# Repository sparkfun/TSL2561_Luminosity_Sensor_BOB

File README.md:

**NOTE:** *This product has been retired from our catalog. If you are looking for more up-to-date info, please check out some of these resources to see how other users are still hacking and improving on this product.*
* *[SparkFun Forum](https://forum.sparkfun.com/)*
* *[Comments Here on GitHub](https://github.com/sparkfun/SparkFun_TSL2561_Arduino_Library/issues)*
* *[IRC Channel](https://www.sparkfun.com/news/263)*

SparkFun TSL2561 Luminosity Sensor Breakout Board
============================================

[*TSL2561 Luminosity Sensor Breakout (SEN-12055)*](https://www.sparkfun.com/products/12055)

This is a breakout board for the AMS/TAOS TSL2561 Luminosity sensor.
This illumination sensor has a flat response across most of the visible spectrum and has an adjustable integration time. 
It communicates via I2C and runs at 3.3V. 

Repository Contents
-------------------
* **/Documentation** - Datasheets and additional information 
* **/Hardware** - Eagle design files (.brd, .sch)
* **/Libraries** - Libraries for use with the TSL2561
* **/Production** - Production panel files (.brd)

Documentation
--------------
* **[Library](https://github.com/sparkfun/SparkFun_TSL2561_Arduino_Library)** - Arduino library for the TSL2561.
* **[Hookup Guide](https://learn.sparkfun.com/tutorials/tsl2561-luminosity-sensor-hookup-guide)** - Basic hookup guide for the TSL2561 Breakout.
* **[SparkFun Fritzing repo](https://github.com/sparkfun/Fritzing_Parts)** - Fritzing diagrams for SparkFun products.
* **[SparkFun 3D Model repo](https://github.com/sparkfun/3D_Models)** - 3D models of SparkFun products. 

License Information
-------------------
This product is _**open source**_! 

The **hardware** is released under [Creative Commons ShareAlike 4.0 International](https://creativecommons.org/licenses/by-sa/4.0/).

The **code** is beerware; if you see me (or any other SparkFun employee) at the local, and you've found our code helpful, please buy us a round!

Please use, reuse, and modify these files as you see fit. Please maintain attribution to SparkFun Electronics and release anything derivative under the same license.

Distributed as-is; no warranty is given.

- Your friends at SparkFun.

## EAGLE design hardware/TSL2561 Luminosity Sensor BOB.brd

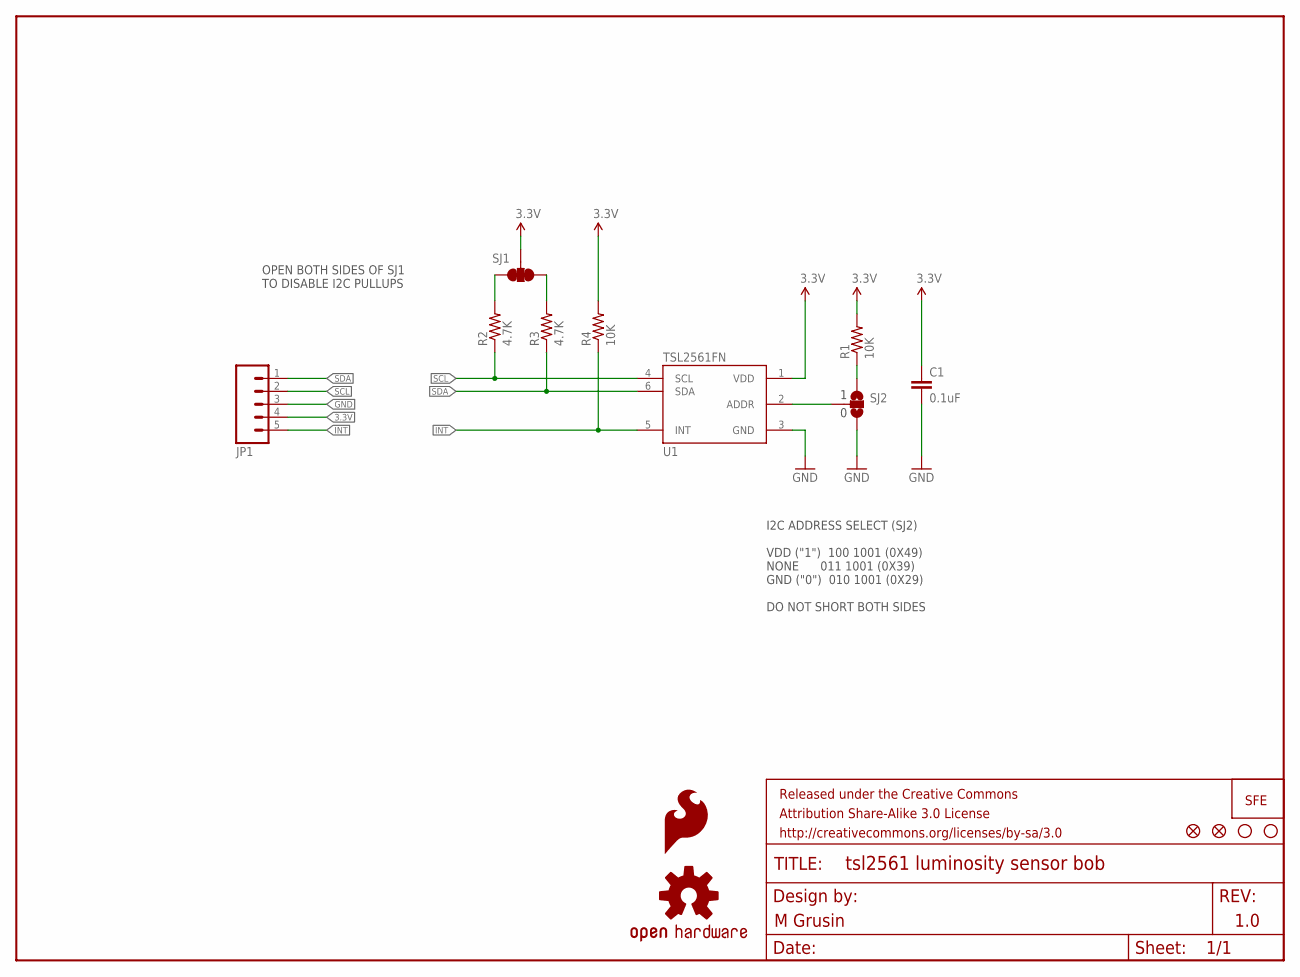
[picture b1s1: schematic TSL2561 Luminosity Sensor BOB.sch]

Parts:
C1: 0.1uF; 0603-CAP
FID1, FID2: FIDUCIALUFIDUCIAL; MICRO-FIDUCIAL
FRAME1: FRAME-LETTER; CREATIVE_COMMONS
JP1: M05_ROUNDONLY_NOSILK; 1X05_ROUNDONLY_NOSILK
LOGO1: OSHW-LOGOS; OSHW-LOGO-S
LOGO2: LOGO-SFENW2; SFE-NEW-WEB
LOGO3: SFE_LOGO_FLAME.1_INCH; SFE_LOGO_FLAME_.1
R1, R4: 10K; 0603-RES
R2, R3: 4.7K; 0603-RES
SJ1: SOLDERJUMPER_2WAYPASTE1&2&3; SJ_3_PASTE1&2&3
SJ2: SOLDERJUMPER_2WAYS; SJ_3
STANDOFF1, STANDOFF2: STAND-OFF
U1: TSL2561FN; FN-6

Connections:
3.3V: C1.1, JP1.4, R1.2, R4.2, SJ1.2, U1.1 (VDD)
GND: C1.2, JP1.3, SJ2.3, U1.3 (GND)
INT: JP1.5, R4.1, U1.5 (INT)
unnamed: R1.1, SJ2.1
unnamed: SJ2.2, U1.2 (ADDR)
unnamed: R3.2, SJ1.1
unnamed: R2.2, SJ1.3
SCL: JP1.2, R2.1, U1.4 (SCL)
SDA: JP1.1, R3.1, U1.6 (SDA)

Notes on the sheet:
I2C ADDRESS SELECT (SJ2) VDD ("1") 100 1001 (0X49) NONE 011 1001 (0X39) GND ("0") 010 1001 (0X29) DO NOT SHORT BOTH SIDES
M Grusin
OPEN BOTH SIDES OF SJ1 TO DISABLE I2C PULLUPS
1.0

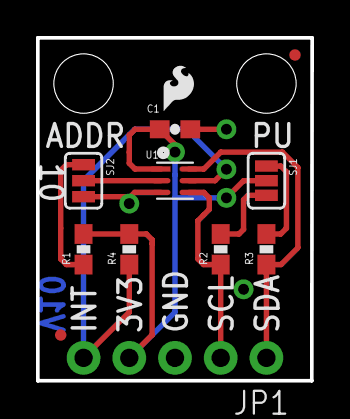
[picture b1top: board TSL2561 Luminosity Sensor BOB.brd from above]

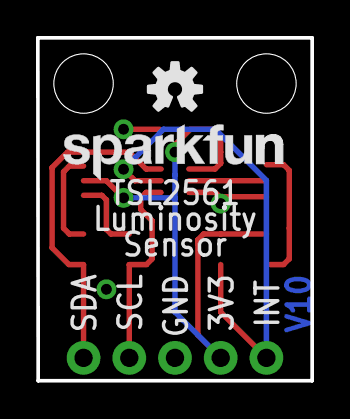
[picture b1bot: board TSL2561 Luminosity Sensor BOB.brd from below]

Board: 2 copper layers, 15.2 x 19.1 mm, 17 parts (2 on the bottom side), 9 nets.

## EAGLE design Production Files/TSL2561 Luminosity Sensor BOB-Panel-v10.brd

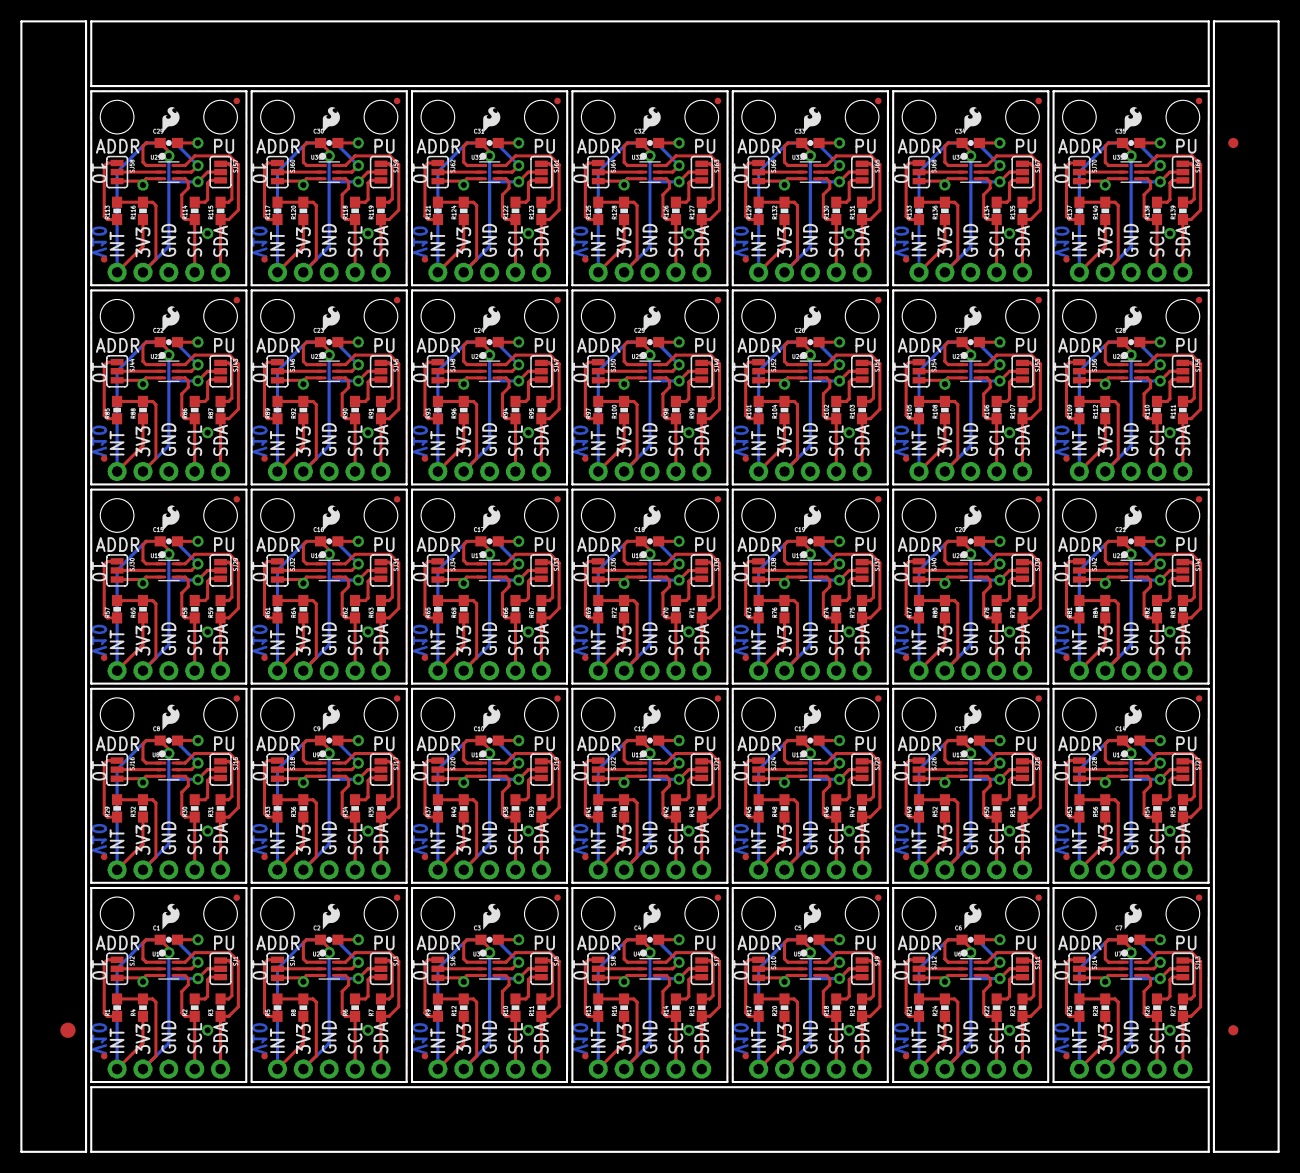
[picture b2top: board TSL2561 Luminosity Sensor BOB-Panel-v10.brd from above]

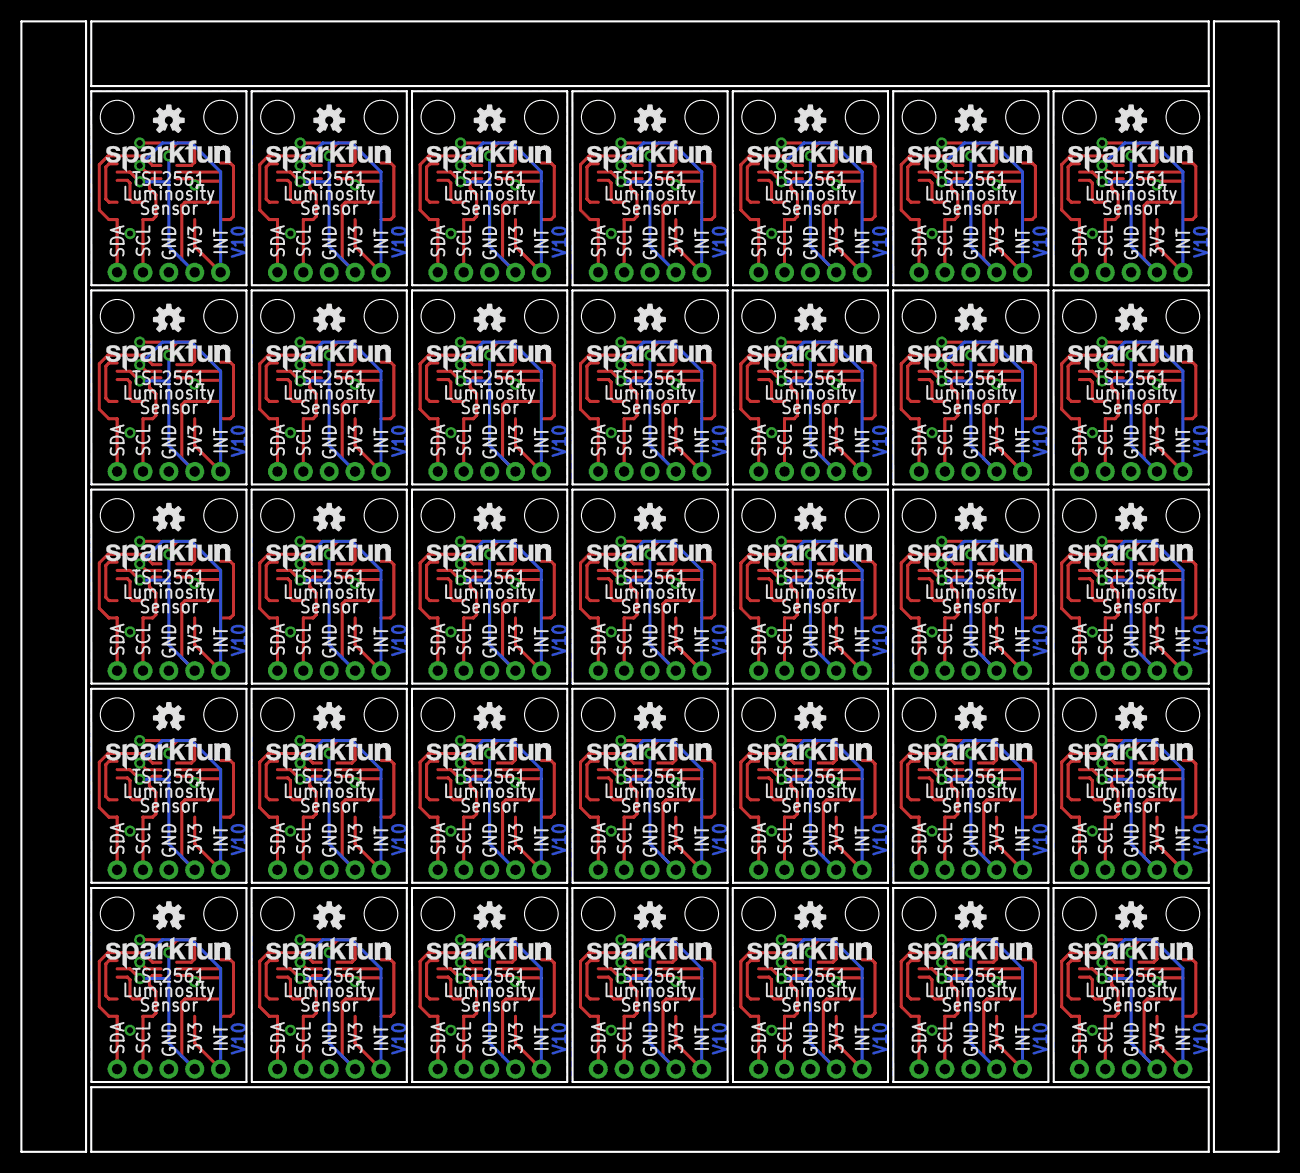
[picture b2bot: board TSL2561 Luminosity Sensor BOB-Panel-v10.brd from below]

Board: 2 copper layers, 123.4 x 111.0 mm, 563 parts (70 on the bottom side), 315 nets.

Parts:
C1, C2, C3, C4, C5, C6, C7, C8, C9, C10, C11, C12, C13, C14, C15, C16, C17, C18, C19, C20, C21, C22, C23, C24, C25, C26, C27, C28, C29, C30, C31, C32, C33, C34, C35: 0.1uF; 0603-CAP
E$1: FIDUCIAL-1.5X3
E$4, E$5: FIDUCIAL-1X2
FID1, FID2, FID3, FID4, FID5, FID6, FID7, FID8, FID9, FID10, FID11, FID12, FID13, FID14, FID15, FID16, FID17, FID18, FID19, FID20, FID21, FID22, FID23, FID24, FID25, FID26, FID27, FID28, FID29, FID30, FID31, FID32, FID33, FID34, FID35, FID36, FID37, FID38, FID39, FID40, FID41, FID42, FID43, FID44, FID45, FID46, FID47, FID48, FID49, FID50, FID51, FID52, FID53, FID54, FID55, FID56, FID57, FID58, FID59, FID60, FID61, FID62, FID63, FID64, FID65, FID66, FID67, FID68, FID69, FID70: FIDUCIALUFIDUCIAL; MICRO-FIDUCIAL
JP1, JP2, JP3, JP4, JP5, JP6, JP7, JP8, JP9, JP10, JP11, JP12, JP13, JP14, JP15, JP16, JP17, JP18, JP19, JP20, JP21, JP22, JP23, JP24, JP25, JP26, JP27, JP28, JP29, JP30, JP31, JP32, JP33, JP34, JP35: 1X05_ROUNDONLY_NOSILK
LOGO1, LOGO4, LOGO7, LOGO10, LOGO13, LOGO16, LOGO19, LOGO22, LOGO25, LOGO28, LOGO31, LOGO34, LOGO37, LOGO40, LOGO43, LOGO46, LOGO49, LOGO52, LOGO55, LOGO58, LOGO61, LOGO64, LOGO67, LOGO70, LOGO73, LOGO76, LOGO79, LOGO82, LOGO85, LOGO88, LOGO91, LOGO94, LOGO97, LOGO100, LOGO103: OSHW-LOGOS; OSHW-LOGO-S
LOGO2, LOGO5, LOGO8, LOGO11, LOGO14, LOGO17, LOGO20, LOGO23, LOGO26, LOGO29, LOGO32, LOGO35, LOGO38, LOGO41, LOGO44, LOGO47, LOGO50, LOGO53, LOGO56, LOGO59, LOGO62, LOGO65, LOGO68, LOGO71, LOGO74, LOGO77, LOGO80, LOGO83, LOGO86, LOGO89, LOGO92, LOGO95, LOGO98, LOGO101, LOGO104: LOGO-SFENW2; SFE-NEW-WEB
LOGO3, LOGO6, LOGO9, LOGO12, LOGO15, LOGO18, LOGO21, LOGO24, LOGO27, LOGO30, LOGO33, LOGO36, LOGO39, LOGO42, LOGO45, LOGO48, LOGO51, LOGO54, LOGO57, LOGO60, LOGO63, LOGO66, LOGO69, LOGO72, LOGO75, LOGO78, LOGO81, LOGO84, LOGO87, LOGO90, LOGO93, LOGO96, LOGO99, LOGO102, LOGO105: SFE_LOGO_FLAME.1_INCH; SFE_LOGO_FLAME_.1
R1, R4, R5, R8, R9, R12, R13, R16, R17, R20, R21, R24, R25, R28, R29, R32, R33, R36, R37, R40, R41, R44, R45, R48, R49, R52, R53, R56, R57, R60, R61, R64, R65, R68, R69, R72, R73, R76, R77, R80, R81, R84, R85, R88, R89, R92, R93, R96, R97, R100, R101, R104, R105, R108, R109, R112, R113, R116, R117, R120, R121, R124, R125, R128, R129, R132, R133, R136, R137, R140: 10K; 0603-RES
R2, R3, R6, R7, R10, R11, R14, R15, R18, R19, R22, R23, R26, R27, R30, R31, R34, R35, R38, R39, R42, R43, R46, R47, R50, R51, R54, R55, R58, R59, R62, R63, R66, R67, R70, R71, R74, R75, R78, R79, R82, R83, R86, R87, R90, R91, R94, R95, R98, R99, R102, R103, R106, R107, R110, R111, R114, R115, R118, R119, R122, R123, R126, R127, R130, R131, R134, R135, R138, R139: 4.7K; 0603-RES
SJ1, SJ3, SJ5, SJ7, SJ9, SJ11, SJ13, SJ15, SJ17, SJ19, SJ21, SJ23, SJ25, SJ27, SJ29, SJ31, SJ33, SJ35, SJ37, SJ39, SJ41, SJ43, SJ45, SJ47, SJ49, SJ51, SJ53, SJ55, SJ57, SJ59, SJ61, SJ63, SJ65, SJ67, SJ69: SJ_3_PASTE1&2&3
SJ2, SJ4, SJ6, SJ8, SJ10, SJ12, SJ14, SJ16, SJ18, SJ20, SJ22, SJ24, SJ26, SJ28, SJ30, SJ32, SJ34, SJ36, SJ38, SJ40, SJ42, SJ44, SJ46, SJ48, SJ50, SJ52, SJ54, SJ56, SJ58, SJ60, SJ62, SJ64, SJ66, SJ68, SJ70: SJ_3
STANDOFF1, STANDOFF2, STANDOFF3, STANDOFF4, STANDOFF5, STANDOFF6, STANDOFF7, STANDOFF8, STANDOFF9, STANDOFF10, STANDOFF11, STANDOFF12, STANDOFF13, STANDOFF14, STANDOFF15, STANDOFF16, STANDOFF17, STANDOFF18, STANDOFF19, STANDOFF20, STANDOFF21, STANDOFF22, STANDOFF23, STANDOFF24, STANDOFF25, STANDOFF26, STANDOFF27, STANDOFF28, STANDOFF29, STANDOFF30, STANDOFF31, STANDOFF32, STANDOFF33, STANDOFF34, STANDOFF35, STANDOFF36, STANDOFF37, STANDOFF38, STANDOFF39, STANDOFF40, STANDOFF41, STANDOFF42, STANDOFF43, STANDOFF44, STANDOFF45, STANDOFF46, STANDOFF47, STANDOFF48, STANDOFF49, STANDOFF50, STANDOFF51, STANDOFF52, STANDOFF53, STANDOFF54, STANDOFF55, STANDOFF56, STANDOFF57, STANDOFF58, STANDOFF59, STANDOFF60, STANDOFF61, STANDOFF62, STANDOFF63, STANDOFF64, STANDOFF65, STANDOFF66, STANDOFF67, STANDOFF68, STANDOFF69, STANDOFF70: STAND-OFF
U1, U2, U3, U4, U5, U6, U7, U8, U9, U10, U11, U12, U13, U14, U15, U16, U17, U18, U19, U20, U21, U22, U23, U24, U25, U26, U27, U28, U29, U30, U31, U32, U33, U34, U35: TSL2561FN; FN-6

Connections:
3.3V: C1.1, JP1.4, R1.2, R4.2, SJ1.2, U1.1
3.3V1: C2.1, JP2.4, R5.2, R8.2, SJ3.2, U2.1
3.3V2: C3.1, JP3.4, R9.2, R12.2, SJ5.2, U3.1
3.3V3: C4.1, JP4.4, R13.2, R16.2, SJ7.2, U4.1
3.3V4: C5.1, JP5.4, R17.2, R20.2, SJ9.2, U5.1
3.3V5: C6.1, JP6.4, R21.2, R24.2, SJ11.2, U6.1
3.3V6: C7.1, JP7.4, R25.2, R28.2, SJ13.2, U7.1
3.3V7: C8.1, JP8.4, R29.2, R32.2, SJ15.2, U8.1
3.3V8: C9.1, JP9.4, R33.2, R36.2, SJ17.2, U9.1
3.3V9: C10.1, JP10.4, R37.2, R40.2, SJ19.2, U10.1
3.3V10: C11.1, JP11.4, R41.2, R44.2, SJ21.2, U11.1
3.3V11: C12.1, JP12.4, R45.2, R48.2, SJ23.2, U12.1
3.3V12: C13.1, JP13.4, R49.2, R52.2, SJ25.2, U13.1
3.3V13: C14.1, JP14.4, R53.2, R56.2, SJ27.2, U14.1
3.3V14: C15.1, JP15.4, R57.2, R60.2, SJ29.2, U15.1
3.3V15: C16.1, JP16.4, R61.2, R64.2, SJ31.2, U16.1
3.3V16: C17.1, JP17.4, R65.2, R68.2, SJ33.2, U17.1
3.3V17: C18.1, JP18.4, R69.2, R72.2, SJ35.2, U18.1
3.3V18: C19.1, JP19.4, R73.2, R76.2, SJ37.2, U19.1
3.3V19: C20.1, JP20.4, R77.2, R80.2, SJ39.2, U20.1
3.3V20: C21.1, JP21.4, R81.2, R84.2, SJ41.2, U21.1
3.3V21: C22.1, JP22.4, R85.2, R88.2, SJ43.2, U22.1
3.3V22: C23.1, JP23.4, R89.2, R92.2, SJ45.2, U23.1
3.3V23: C24.1, JP24.4, R93.2, R96.2, SJ47.2, U24.1
3.3V24: C25.1, JP25.4, R97.2, R100.2, SJ49.2, U25.1
3.3V25: C26.1, JP26.4, R101.2, R104.2, SJ51.2, U26.1
3.3V26: C27.1, JP27.4, R105.2, R108.2, SJ53.2, U27.1
3.3V27: C28.1, JP28.4, R109.2, R112.2, SJ55.2, U28.1
3.3V28: C29.1, JP29.4, R113.2, R116.2, SJ57.2, U29.1
3.3V29: C30.1, JP30.4, R117.2, R120.2, SJ59.2, U30.1
3.3V30: C31.1, JP31.4, R121.2, R124.2, SJ61.2, U31.1
3.3V31: C32.1, JP32.4, R125.2, R128.2, SJ63.2, U32.1
3.3V32: C33.1, JP33.4, R129.2, R132.2, SJ65.2, U33.1
3.3V33: C34.1, JP34.4, R133.2, R136.2, SJ67.2, U34.1
3.3V34: C35.1, JP35.4, R137.2, R140.2, SJ69.2, U35.1
GND: C1.2, JP1.3, SJ2.3, U1.3
GND1: C2.2, JP2.3, SJ4.3, U2.3
GND2: C3.2, JP3.3, SJ6.3, U3.3
GND3: C4.2, JP4.3, SJ8.3, U4.3
GND4: C5.2, JP5.3, SJ10.3, U5.3
GND5: C6.2, JP6.3, SJ12.3, U6.3
GND6: C7.2, JP7.3, SJ14.3, U7.3
GND7: C8.2, JP8.3, SJ16.3, U8.3
GND8: C9.2, JP9.3, SJ18.3, U9.3
GND9: C10.2, JP10.3, SJ20.3, U10.3
GND10: C11.2, JP11.3, SJ22.3, U11.3
GND11: C12.2, JP12.3, SJ24.3, U12.3
GND12: C13.2, JP13.3, SJ26.3, U13.3
GND13: C14.2, JP14.3, SJ28.3, U14.3
GND14: C15.2, JP15.3, SJ30.3, U15.3
GND15: C16.2, JP16.3, SJ32.3, U16.3
GND16: C17.2, JP17.3, SJ34.3, U17.3
GND17: C18.2, JP18.3, SJ36.3, U18.3
GND18: C19.2, JP19.3, SJ38.3, U19.3
GND19: C20.2, JP20.3, SJ40.3, U20.3
GND20: C21.2, JP21.3, SJ42.3, U21.3
GND21: C22.2, JP22.3, SJ44.3, U22.3
GND22: C23.2, JP23.3, SJ46.3, U23.3
GND23: C24.2, JP24.3, SJ48.3, U24.3
GND24: C25.2, JP25.3, SJ50.3, U25.3
GND25: C26.2, JP26.3, SJ52.3, U26.3
GND26: C27.2, JP27.3, SJ54.3, U27.3
GND27: C28.2, JP28.3, SJ56.3, U28.3
GND28: C29.2, JP29.3, SJ58.3, U29.3
GND29: C30.2, JP30.3, SJ60.3, U30.3
GND30: C31.2, JP31.3, SJ62.3, U31.3
GND31: C32.2, JP32.3, SJ64.3, U32.3
GND32: C33.2, JP33.3, SJ66.3, U33.3
GND33: C34.2, JP34.3, SJ68.3, U34.3
GND34: C35.2, JP35.3, SJ70.3, U35.3
INT: JP1.5, R4.1, U1.5
INT1: JP2.5, R8.1, U2.5
INT2: JP3.5, R12.1, U3.5
INT3: JP4.5, R16.1, U4.5
INT4: JP5.5, R20.1, U5.5
INT5: JP6.5, R24.1, U6.5
INT6: JP7.5, R28.1, U7.5
INT7: JP8.5, R32.1, U8.5
INT8: JP9.5, R36.1, U9.5
INT9: JP10.5, R40.1, U10.5
INT10: JP11.5, R44.1, U11.5
INT11: JP12.5, R48.1, U12.5
INT12: JP13.5, R52.1, U13.5
INT13: JP14.5, R56.1, U14.5
INT14: JP15.5, R60.1, U15.5
INT15: JP16.5, R64.1, U16.5
INT16: JP17.5, R68.1, U17.5
INT17: JP18.5, R72.1, U18.5
INT18: JP19.5, R76.1, U19.5
INT19: JP20.5, R80.1, U20.5
INT20: JP21.5, R84.1, U21.5
INT21: JP22.5, R88.1, U22.5
INT22: JP23.5, R92.1, U23.5
INT23: JP24.5, R96.1, U24.5
INT24: JP25.5, R100.1, U25.5
INT25: JP26.5, R104.1, U26.5
INT26: JP27.5, R108.1, U27.5
INT27: JP28.5, R112.1, U28.5
INT28: JP29.5, R116.1, U29.5
INT29: JP30.5, R120.1, U30.5
INT30: JP31.5, R124.1, U31.5
INT31: JP32.5, R128.1, U32.5
INT32: JP33.5, R132.1, U33.5
INT33: JP34.5, R136.1, U34.5
INT34: JP35.5, R140.1, U35.5
unnamed: R5.1, SJ4.1
unnamed: R1.1, SJ2.1
unnamed: SJ2.2, U1.2
unnamed: SJ4.2, U2.2
unnamed: R7.2, SJ3.1
unnamed: R6.2, SJ3.3
unnamed: R9.1, SJ6.1
unnamed: R3.2, SJ1.1
unnamed: R2.2, SJ1.3
unnamed: SJ6.2, U3.2
unnamed: R11.2, SJ5.1
unnamed: R10.2, SJ5.3
unnamed: R13.1, SJ8.1
unnamed: SJ8.2, U4.2
unnamed: R15.2, SJ7.1
unnamed: R14.2, SJ7.3
unnamed: R17.1, SJ10.1
unnamed: SJ10.2, U5.2
unnamed: R19.2, SJ9.1
unnamed: R18.2, SJ9.3
unnamed: R21.1, SJ12.1
unnamed: SJ12.2, U6.2
unnamed: R23.2, SJ11.1
unnamed: R22.2, SJ11.3
unnamed: R25.1, SJ14.1
unnamed: SJ14.2, U7.2
unnamed: R27.2, SJ13.1
unnamed: R26.2, SJ13.3
unnamed: R29.1, SJ16.1
unnamed: SJ16.2, U8.2
unnamed: R31.2, SJ15.1
unnamed: R30.2, SJ15.3
unnamed: R33.1, SJ18.1
unnamed: SJ18.2, U9.2
unnamed: R35.2, SJ17.1
unnamed: R34.2, SJ17.3
unnamed: R37.1, SJ20.1
unnamed: SJ20.2, U10.2
unnamed: R39.2, SJ19.1
unnamed: R38.2, SJ19.3
unnamed: R41.1, SJ22.1
unnamed: SJ22.2, U11.2
unnamed: R43.2, SJ21.1
unnamed: R42.2, SJ21.3
unnamed: R45.1, SJ24.1
unnamed: SJ24.2, U12.2
unnamed: R47.2, SJ23.1
unnamed: R46.2, SJ23.3
unnamed: R49.1, SJ26.1
unnamed: SJ26.2, U13.2
unnamed: R51.2, SJ25.1
unnamed: R50.2, SJ25.3
unnamed: R53.1, SJ28.1
unnamed: SJ28.2, U14.2
unnamed: R55.2, SJ27.1
unnamed: R54.2, SJ27.3
unnamed: R57.1, SJ30.1
unnamed: SJ30.2, U15.2
unnamed: R59.2, SJ29.1
unnamed: R58.2, SJ29.3
unnamed: R61.1, SJ32.1
unnamed: SJ32.2, U16.2
unnamed: R63.2, SJ31.1
unnamed: R62.2, SJ31.3
unnamed: R65.1, SJ34.1
unnamed: SJ34.2, U17.2
unnamed: R67.2, SJ33.1
unnamed: R66.2, SJ33.3
unnamed: R69.1, SJ36.1
unnamed: SJ36.2, U18.2
unnamed: R71.2, SJ35.1
unnamed: R70.2, SJ35.3
unnamed: R73.1, SJ38.1
unnamed: SJ38.2, U19.2
unnamed: R75.2, SJ37.1
unnamed: R74.2, SJ37.3
unnamed: R77.1, SJ40.1
unnamed: SJ40.2, U20.2
unnamed: R79.2, SJ39.1
unnamed: R78.2, SJ39.3
unnamed: R81.1, SJ42.1
unnamed: SJ42.2, U21.2
unnamed: R83.2, SJ41.1
unnamed: R82.2, SJ41.3
unnamed: R85.1, SJ44.1
unnamed: SJ44.2, U22.2
unnamed: R87.2, SJ43.1
unnamed: R86.2, SJ43.3
unnamed: R89.1, SJ46.1
unnamed: SJ46.2, U23.2
unnamed: R91.2, SJ45.1
unnamed: R90.2, SJ45.3
unnamed: R93.1, SJ48.1
unnamed: SJ48.2, U24.2
unnamed: R95.2, SJ47.1
unnamed: R94.2, SJ47.3
unnamed: R97.1, SJ50.1
unnamed: SJ50.2, U25.2
unnamed: R99.2, SJ49.1
unnamed: R98.2, SJ49.3
unnamed: R101.1, SJ52.1
unnamed: SJ52.2, U26.2
unnamed: R103.2, SJ51.1
unnamed: R102.2, SJ51.3
unnamed: R105.1, SJ54.1
unnamed: SJ54.2, U27.2
unnamed: R107.2, SJ53.1
unnamed: R106.2, SJ53.3
unnamed: R109.1, SJ56.1
unnamed: SJ56.2, U28.2
unnamed: R111.2, SJ55.1
unnamed: R110.2, SJ55.3
unnamed: R113.1, SJ58.1
unnamed: SJ58.2, U29.2
unnamed: R115.2, SJ57.1
unnamed: R114.2, SJ57.3
unnamed: R117.1, SJ60.1
unnamed: SJ60.2, U30.2
unnamed: R119.2, SJ59.1
unnamed: R118.2, SJ59.3
unnamed: R121.1, SJ62.1
unnamed: SJ62.2, U31.2
unnamed: R123.2, SJ61.1
unnamed: R122.2, SJ61.3
unnamed: R125.1, SJ64.1
unnamed: SJ64.2, U32.2
unnamed: R127.2, SJ63.1
unnamed: R126.2, SJ63.3
unnamed: R129.1, SJ66.1
unnamed: SJ66.2, U33.2
unnamed: R131.2, SJ65.1
unnamed: R130.2, SJ65.3
unnamed: R133.1, SJ68.1
unnamed: SJ68.2, U34.2
unnamed: R135.2, SJ67.1
unnamed: R134.2, SJ67.3
unnamed: R137.1, SJ70.1
unnamed: SJ70.2, U35.2
unnamed: R139.2, SJ69.1
unnamed: R138.2, SJ69.3
SCL: JP1.2, R2.1, U1.4
SCL1: JP2.2, R6.1, U2.4
SCL2: JP3.2, R10.1, U3.4
SCL3: JP4.2, R14.1, U4.4
SCL4: JP5.2, R18.1, U5.4
SCL5: JP6.2, R22.1, U6.4
SCL6: JP7.2, R26.1, U7.4
SCL7: JP8.2, R30.1, U8.4
SCL8: JP9.2, R34.1, U9.4
SCL9: JP10.2, R38.1, U10.4
SCL10: JP11.2, R42.1, U11.4
SCL11: JP12.2, R46.1, U12.4
SCL12: JP13.2, R50.1, U13.4
SCL13: JP14.2, R54.1, U14.4
SCL14: JP15.2, R58.1, U15.4
SCL15: JP16.2, R62.1, U16.4
SCL16: JP17.2, R66.1, U17.4
SCL17: JP18.2, R70.1, U18.4
SCL18: JP19.2, R74.1, U19.4
SCL19: JP20.2, R78.1, U20.4
SCL20: JP21.2, R82.1, U21.4
SCL21: JP22.2, R86.1, U22.4
SCL22: JP23.2, R90.1, U23.4
SCL23: JP24.2, R94.1, U24.4
SCL24: JP25.2, R98.1, U25.4
SCL25: JP26.2, R102.1, U26.4
SCL26: JP27.2, R106.1, U27.4
SCL27: JP28.2, R110.1, U28.4
SCL28: JP29.2, R114.1, U29.4
SCL29: JP30.2, R118.1, U30.4
SCL30: JP31.2, R122.1, U31.4
SCL31: JP32.2, R126.1, U32.4
SCL32: JP33.2, R130.1, U33.4
SCL33: JP34.2, R134.1, U34.4
SCL34: JP35.2, R138.1, U35.4
SDA: JP1.1, R3.1, U1.6
SDA1: JP2.1, R7.1, U2.6
SDA2: JP3.1, R11.1, U3.6
SDA3: JP4.1, R15.1, U4.6
SDA4: JP5.1, R19.1, U5.6
SDA5: JP6.1, R23.1, U6.6
SDA6: JP7.1, R27.1, U7.6
SDA7: JP8.1, R31.1, U8.6
SDA8: JP9.1, R35.1, U9.6
SDA9: JP10.1, R39.1, U10.6
SDA10: JP11.1, R43.1, U11.6
SDA11: JP12.1, R47.1, U12.6
SDA12: JP13.1, R51.1, U13.6
SDA13: JP14.1, R55.1, U14.6
SDA14: JP15.1, R59.1, U15.6
SDA15: JP16.1, R63.1, U16.6
SDA16: JP17.1, R67.1, U17.6
SDA17: JP18.1, R71.1, U18.6
SDA18: JP19.1, R75.1, U19.6
SDA19: JP20.1, R79.1, U20.6
SDA20: JP21.1, R83.1, U21.6
SDA21: JP22.1, R87.1, U22.6
SDA22: JP23.1, R91.1, U23.6
SDA23: JP24.1, R95.1, U24.6
SDA24: JP25.1, R99.1, U25.6
SDA25: JP26.1, R103.1, U26.6
SDA26: JP27.1, R107.1, U27.6
SDA27: JP28.1, R111.1, U28.6
SDA28: JP29.1, R115.1, U29.6
SDA29: JP30.1, R119.1, U30.6
SDA30: JP31.1, R123.1, U31.6
SDA31: JP32.1, R127.1, U32.6
SDA32: JP33.1, R131.1, U33.6
SDA33: JP34.1, R135.1, U34.6
SDA34: JP35.1, R139.1, U35.6

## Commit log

2013-08-27 clean up
2013-09-10 Updated prototype to V02
    Per discussion with Pete L, replaced T package with FN package.
2013-09-10 Minor changes
2013-09-10 Minor rename
2013-09-10 Minor update
2013-11-01 library and example in-progress
2013-11-08 in-progress
2013-11-11 Review for reds (hardware only)
2013-11-11 Hardware version 1.0
    added micro-fiducials
2013-11-12 Created Panel
2013-11-25 library in progress
2013-11-27 in progress
    Working word read and write (finally!)
    Note that block read works OK on this chip, but not block write
2013-12-09 library for review
2013-12-26 Release functionality, minor comment updates to come
2013-12-26 Updating repo structure and README
2013-12-27 Release library and example
2013-12-27 Added links to readme.md
2014-05-13 Fixing gain normalization
2015-01-29 Updating BRD/SCH files to current lib parts
2015-02-17 Fixed a bug (wrong type) that did notallow the library to compile on Arduino 1.6.0
2015-03-31 Fixing directory/file names
2015-04-24 Initial Commit
    Updating for Arduino 1.6+ Library Manager
2015-04-24 Updating README
    Updating README
2015-04-24 Splitting Library in to separate repo
    Splitting Library in to separate repo
2015-04-24 Squashed 'Libraries/Arduino/' content from commit 0efad21
    git-subtree-dir: Libraries/Arduino
    git-subtree-split: 0efad215c861a0b28a588bdb130cdf52d871eb24
2015-04-24 Edited the example
    Edited the example
2015-04-24 Fixed folder snafu
    Fixed folder snafu
2015-05-19 Adding back in hardware files and datasheet
2015-05-19 Squashed 'Libraries/Arduino/' changes from 0efad21..827ec28
    git-subtree-dir: Libraries/Arduino
    git-subtree-split: 827ec2831706ae7cf1d63d30cc90fc6844a96369
2015-05-19 Fixing README typo
2015-05-19 Squashed 'Libraries/Arduino/' content from commit 827ec28
    git-subtree-dir: Libraries/Arduino
    git-subtree-split: 827ec2831706ae7cf1d63d30cc90fc6844a96369
2018-07-16 Bug in line 266 I think
    correct version: if (writeByte(TSL2561_REG_INTCTL,((control & 0B00000011) << 4) | (persist & 0B00001111)))
2018-07-25 Retired
    Added notice that the product is retired.
2018-07-25 Fixed mask in CPP line 266 per user wollenwald (thanks!)

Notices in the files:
parts and their libraries:
SparkFun-Aesthetics: Licensing: CC v3.0 Share-Alike You are welcome to use this library for commercial purposes.
SparkFun-Aesthetics: Released under the Creative Commons Attribution Share-Alike 3.0 License
SparkFun-Aesthetics: http://creativecommons.org/licenses/by-sa/3.0
